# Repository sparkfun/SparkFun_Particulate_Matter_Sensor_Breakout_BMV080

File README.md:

SparkFun Air Quality PM1/PM2.5/PM10 Sensor - BMV080 (Qwiic)
========================================

[*SparkFun Air Quality PM1/PM2.5/PM10 Sensor - BMV080 (Qwiic) (SEN-26554)*](https://www.sparkfun.com/sparkfun-air-quality-pm1-pm2-5-pm10-sensor-bmv080-qwiic.html)

The SparkFun Qwiic Particulate Matter Sensor - BMV080 is an ultra-small, fan-less air quality sensor for sensing PM2.5 particulate matter! Within the enclosure is a breakout board that breaks out Bosch's BMV080, the world's smallest PM1 and PM2.5 air quality sensor. The sensing element measures merely 4.2mm x 3.5mm x 3.1mm (W x L x H), which is more than 450 times smaller than any comparable device on the market. The innovative design is based on ultra-compact lasers with integrated photodiodes. The sensor applies sophisticated algorithms to measure PM1 and PM2.5 concentrations directly in free space, without requiring an intrusive fan.

Repository Contents
-------------------

* **.github/workflows** - YAML files used for GitHub Actions and GitHub Pages/mkdocs
* **/Enclosure** - Enclosure files
* **/Hardware** - KiCad design files (.kicad_pcb, .kicad_sch, .kicad_pro)
  * **/Production** - Production panel files (.kicad_pcb)
* **/docs** - Online documentation files
  * **/assets** - Folder containing all the file assets used for product documentation
    * **/board_files** - Copy of design files used for product documentation
    * **/component_documentation** - Datasheets and manuals for hardware components
    * **/img** - Images for product documentation
  * **/github** - Files stating how to contribute and filing issues used for product documentation
  * **/javascript** - Folder containing custom javascript used for product documentation
  * **/stylesheet** - Folder containing CSS files used for product documentation
* **/overrides** - Customization files used for product documentation
  * **/.icons** - Icons used for GitHub used for product documentation
  * **./partials** - Used for product documentation

Documentation
--------------
* **[Library](https://github.com/sparkfun/SparkFun_BMV080_Arduino_Library/)** - Arduino library for the SparkFun Air Quality PM1/PM2.5/PM10 Sensor - BMV080 (Qwiic).
* **[Hookup Guide](https://docs.sparkfun.com/SparkFun_Particulate_Matter_Sensor_Breakout_BMV080)** - Basic hookup guide for the SparkFun Air Quality PM1/PM2.5/PM10 Sensor - BMV080 (Qwiic).

Product Versions
----------------
* [SEN-26554](https://www.sparkfun.com/products/ - SparkFun Air Quality PM1/PM2.5/PM10 Sensor - BMV080 (Qwiic) 

License Information
-------------------

This product is _**open source**_!

Please review the LICENSE.md file for license information.

If you have any questions or concerns on licensing, please contact technical support on our [SparkFun forums](https://community.sparkfun.com/c/community/general-chit-chat/37).

Distributed as-is; no warranty is given.

- Your friends at SparkFun.

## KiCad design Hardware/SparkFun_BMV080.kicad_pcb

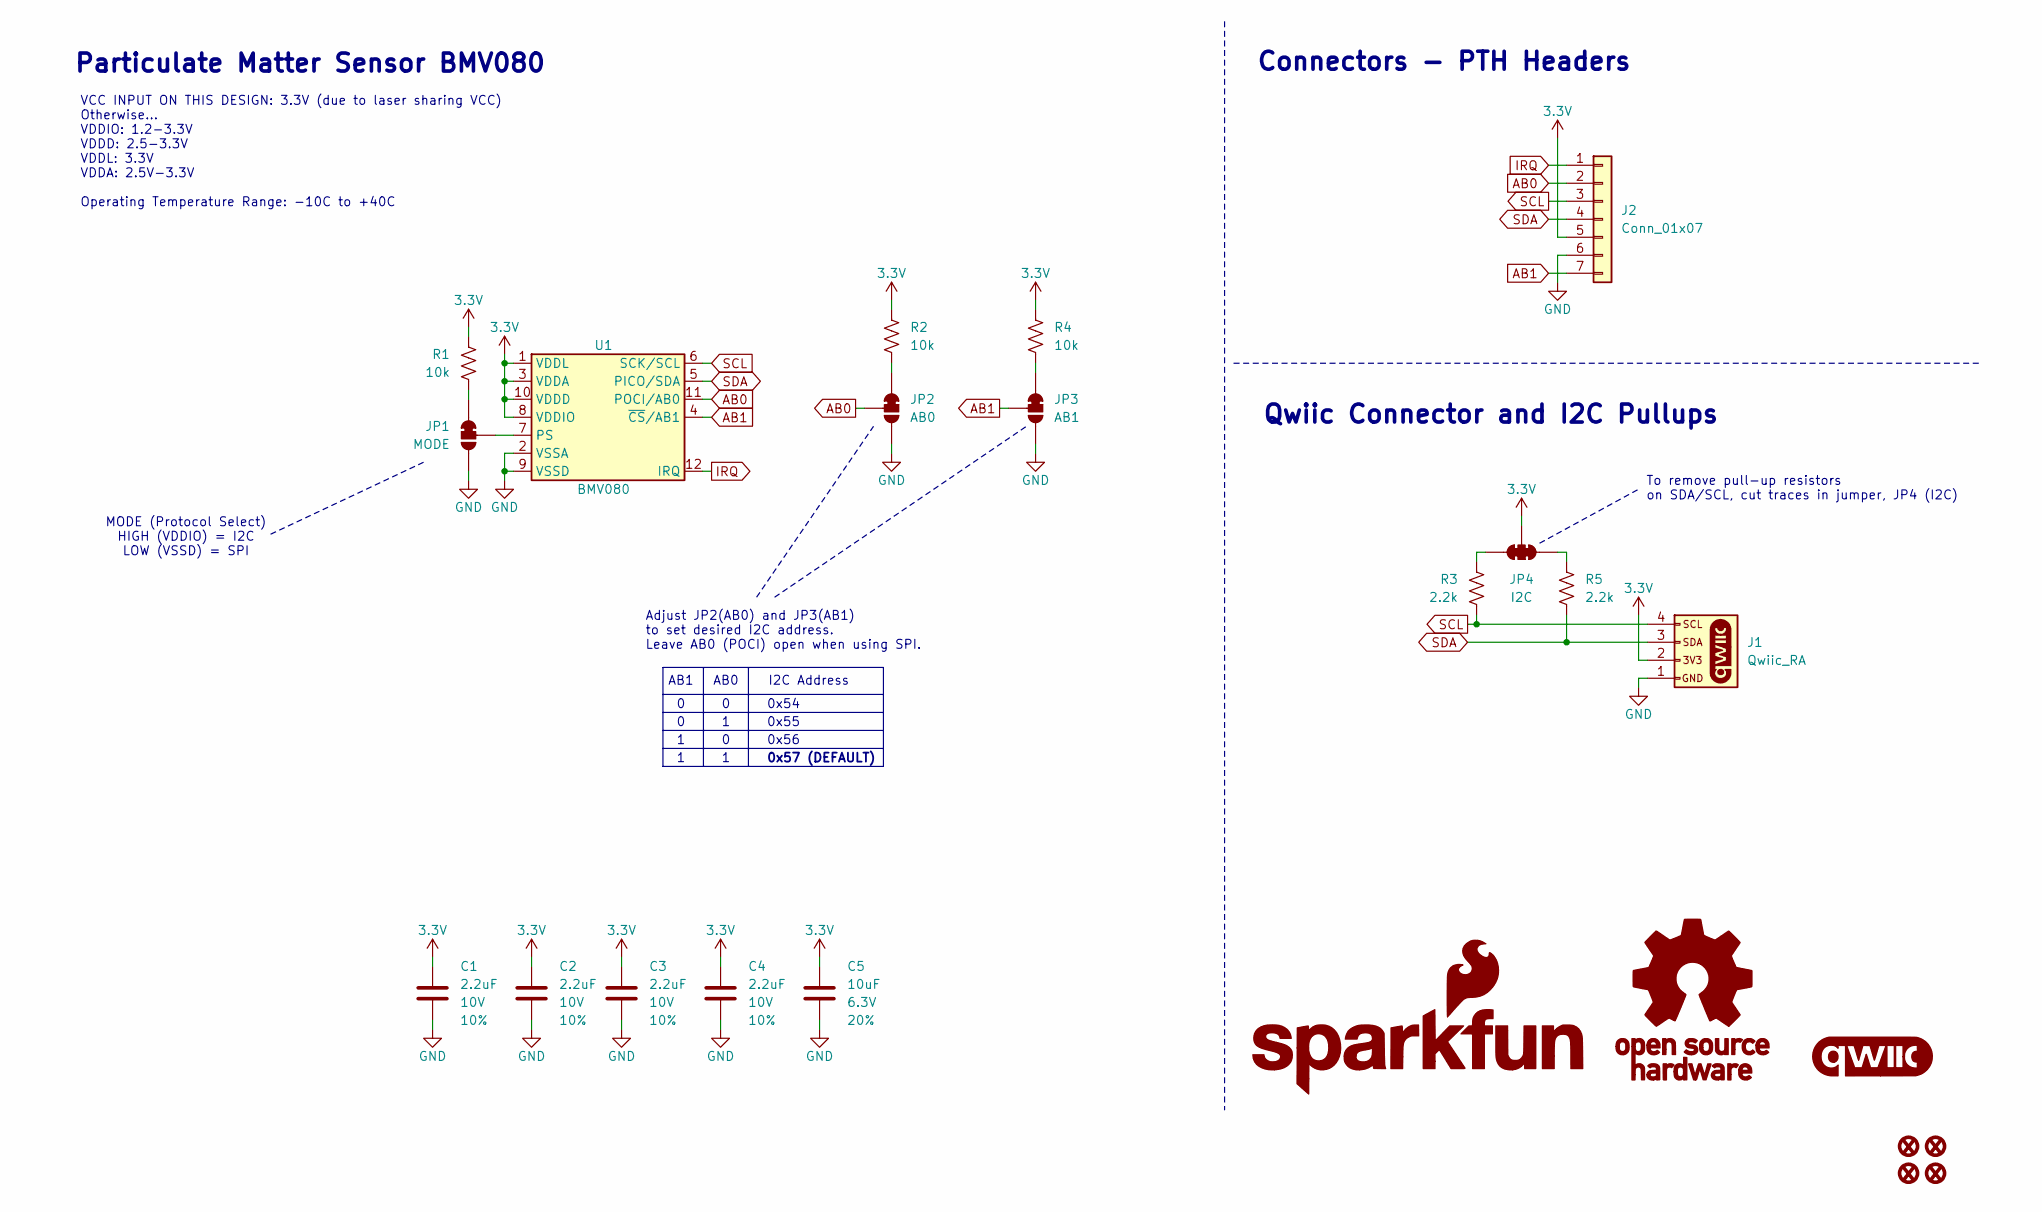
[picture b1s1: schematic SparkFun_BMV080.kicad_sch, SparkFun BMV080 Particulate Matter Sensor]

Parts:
C1, C2, C3, C4: 2.2uF; C_0402_1005Metric; Voltage 10V; Tolerance 10%
C5: 10uF; C_0603_1608Metric; Voltage 6.3V; Tolerance 20%
FID1, FID2, FID3, FID4: Fiducial_0.5mm; Fiducial_0.5mm_Mask1mm
G1: OSHW_Logo; Creative_Commons_License
G2: SparkFun_Logo
G3: qwiic_Logo
J1: Qwiic_RA; JST_SMD_1.0mm-4_RA
J2: Conn_01x07; 1x07
JP1: MODE; Jumper_3_NC-1_Trace_NoSilk
JP2: AB0; Jumper_3_NC-1_Trace_NoSilk
JP3: AB1; Jumper_3_NC-1_Trace_NoSilk
JP4: I2C; Jumper_3_NC-2_Trace_NoSilk
R1, R2, R4: 10k; R_0402_1005Metric
R3, R5: 2.2k; R_0402_1005Metric
U1: BMV080; FPC_0.3mm-13

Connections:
3.3V: C1.1, C2.1, C3.1, C4.1, C5.1, J1.2, J2.5, JP4.2 (C), R1.1, R2.1, R4.1, U1.1 (VDDL), U1.3 (VDDA), U1.8 (VDDIO), U1.10 (VDDD)
AB0: J2.2, JP2.2 (C), U1.11 (POCI/AB0)
AB1: J2.7, JP3.2 (C), U1.4 (~CS/AB1)
GND: C1.2, C2.2, C3.2, C4.2, C5.2, J1.1, J2.6, JP1.3 (B), JP2.3 (B), JP3.3 (B), U1.2 (VSSA), U1.9 (VSSD)
IRQ: J2.1, U1.12 (IRQ)
unnamed: JP1.1 (A), R1.2
unnamed: JP1.2 (C), U1.7 (PS)
unnamed: JP2.1 (A), R2.2
unnamed: JP3.1 (A), R4.2
unnamed: JP4.1 (A), R5.2
unnamed: JP4.3 (B), R3.2
SCL: J1.4, J2.3, R3.1, U1.6 (SCK/SCL)
SDA: J1.3, J2.4, R5.1, U1.5 (PICO/SDA)

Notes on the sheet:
0x54
MODE (Protocol Select) HIGH (VDDIO) = I2C LOW (VSSD) = SPI
AB1
Connectors - PTH Headers
0x57 (DEFAULT)
VCC INPUT ON THIS DESIGN: 3.3V (due to laser sharing VCC) Otherwise... VDDIO: 1.2-3.3V VDDD: 2.5-3.3V VDDL: 3.3V VDDA: 2.5V-3.3V Operating Temperature Range: -10C to +40C
Particulate Matter Sensor BMV080
AB0
0x56
I2C Address
Adjust JP2(AB0) and JP3(AB1) to set desired I2C address. Leave AB0 (POCI) open when using SPI.
0x55
To remove pull-up resistors on SDA/SCL, cut traces in jumper, JP4 (I2C)
Qwiic Connector and I2C Pullups

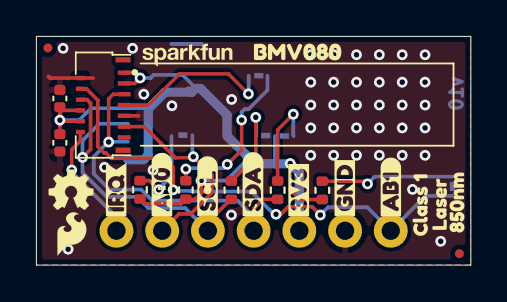
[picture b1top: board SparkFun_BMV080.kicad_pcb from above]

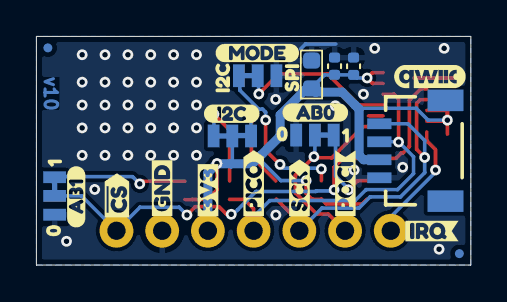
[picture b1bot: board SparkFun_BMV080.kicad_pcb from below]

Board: 2 copper layers, 24.1 x 12.7 mm, 51 parts (27 on the bottom side), 13 nets.

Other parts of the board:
Ref**: Val**; OSHW_Logo_2.5mm
kibuzzard-66BFB450: G***; kibuzzard-66BFB450
kibuzzard-66BFBF9D, kibuzzard-66BFBF9D#2: G***; kibuzzard-66BFBF9D
kibuzzard-66BFBF23: G***; kibuzzard-66BFBF23
kibuzzard-66BFBF70, kibuzzard-66BFBF70#2: G***; kibuzzard-66BFBF70
kibuzzard-66BFC0D2: G***; kibuzzard-66BFC0D2
kibuzzard-66BFC2FE: G***; kibuzzard-66BFC2FE
kibuzzard-66BFC09F: G***; kibuzzard-66BFC09F
kibuzzard-66BFC045: G***; kibuzzard-66BFC045
kibuzzard-66BFC108: G***; kibuzzard-66BFC108
kibuzzard-66BFC288: G***; kibuzzard-66BFC288
kibuzzard-66C3B2A1: G***; kibuzzard-66C3B2A1
kibuzzard-66C3B2DA: G***; kibuzzard-66C3B2DA
kibuzzard-66C3B2FA, kibuzzard-66C3B2FA#2: G***; kibuzzard-66C3B2FA
kibuzzard-66C3B3B1: G***; kibuzzard-66C3B3B1
kibuzzard-66C3B3D3: G***; kibuzzard-66C3B3D3
kibuzzard-66C3B30A, kibuzzard-66C3B30A#2: G***; kibuzzard-66C3B30A
kibuzzard-66C3B31E: G***; kibuzzard-66C3B31E
kibuzzard-66C3B369: G***; kibuzzard-66C3B369
kibuzzard-66C4B81D: G***; kibuzzard-66C4B81D
kibuzzard-66C7A36E: G***; kibuzzard-66C7A36E
kibuzzard-66C77290: G***; kibuzzard-66C77290
kibuzzard-67250BE2: G***; kibuzzard-67250BE2
kibuzzard-67250CD2: G***; kibuzzard-67250CD2
kibuzzard-67250CEE: G***; kibuzzard-67250CEE

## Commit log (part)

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2024-08-16 Layout work
2024-08-19 moved hw files into Hardware folder
2024-08-19 updated gitignore
2024-08-19 moved step file
2024-08-19 schematic cleanup and reroute
    -added section divider lines and section titles
    -jumper reference and naming corrected, rotated text in sch to all horizontal
    -added company and defined by:
    -rearranged part name and value texts for calrity
    -moved logos in sch to proper location
    -moved to vertical qwiic connector
2024-08-20 changed bypass caps to larger value of 2.2uF
    -bypass caps bumped up from 1.0uF to 2.2uF as per recommended in datasheet
2024-08-20 jumpers to no silk outline and prod_id on ic
2024-08-20 measures and more
    -add measures
    -add copper finish
    -add ordering instructions
    -DRC fixes
2024-08-20 grid and molex connector FP correction
    -set grid origin point to top left of PCB edge
    -corrected molex connecto FP - width of mounting pads X position was 2.52 and now is 2.51
2024-08-20 nudged via next to mounting pad for DRC correction
2024-08-20 molex connector outline in FP
2024-08-20 molex fp work
    -removed extra **VAL text object
    -moved INSERT THIS END to user.1
    -added connector ds link in the FP
2024-08-20 molext connector ds link in fp
2024-08-20 corrected position of NC pin 13 in symbol
2024-08-20 CSB is active low in symbol
2024-08-20 drc exlusions
2024-08-21 pre-review last second updates
    -added VCC input requirements and ranges into sch
    -added temp range to sch
    -added pin 1 indicator silk to molex connector
    -added extra GRND trace connection on pad 2 of molex connector
2024-08-21 sensor position outline correction and more
    -added F.Fab and F.Silk outline for sensor - to help with correctly showing position on PCB
    -changed PROD_ID to connector for the sensor
    -made v01 in copper "knockout" style
    -adjusted F.Mask to match the area of the sensor we are supposed to use thermal tape on
    -adjusted B.Mask to match our small heat sink.
2024-08-21 added SFE and OSHW logos
2024-08-21 dimensions update and resistor line up
2024-08-21 moved AB1/CS header onto 0.5 grid for perf board/breadboard
2024-08-21 DRC exclusions
2024-08-22 checklist run eng
    -sch tightening
    -sch jumpers text notes
    -set solder mask expansion to 0.05mm
    -added active low line on top of CS label silk
    -SCL silk label set to input end flag type
2024-08-22 Initial Push GitHub Pages
2024-08-22 acid trap fix on gnd connection coming off Molex
2024-08-22 -tiny tweaks before ordering v01
    -updated measures on AB1 header
    -updated F.FAB drawing of plastic on molex to better estimate reflow position
    -moved NC into symbol box to avoid accidentally netting to it
    -CSB is now CS with a line
    -SCK clock silk label is round
2024-08-22 proto panel 2x2 of v01
2024-08-23 panel v01b - meet size requirement for vscores
    -expanded outer tabs to meet 70mmx70mm requirement for vscores
2024-10-21 housing design - slot style v26
2024-10-22 v27 slight enlarging of slots
2024-11-01 v02 pcb protos v29a enclosure
    -RA qwiic connector
    -removed standoffs
    -single pth header row now includes CS
    -moved pth header upwards to clear enclosure slot
    -decreased width from 1 inch to 0.95 inch
2024-11-01 PCB dimensions updated/added
2024-11-01 update libraries and 3d models
2024-11-04 mounting flanges
2024-11-06 flange tweaking
2024-11-14 bumping version to v10
2024-11-14 removing FreeCAD backup files
2024-11-14 pre-review changes
    -adjusted 3.3V pads route away on FPC to avoid oddities and promote even reflow.
    -added gnd via near AB1 header to avoid GND pour antenna.
    -pulled trace away from I2C jumper to avoid slicing.
    -nudged via to avoid acid trap near AB0 jumper.
    -nudges via near SDA pad on FPC to avoid acid trap
2024-11-14 FPC 3d model position correction
2024-11-14 Added sensor 3d model
2024-11-15 Update 3D model
2024-11-25 Changed C5 from DNP to populated
2024-11-25 ordering instructions updated to RED
2024-11-25 production pcb panel v10
2024-11-26 V32 housing - unify parts and exported STL files
    -V32 housing design verified on inhouse resin printer
    -unified (aka Fusion in freeCAD) bodies to a single body for mesh export as STL
    -utilized higher precision settings for TSL export (surface dev: 10um, angular dev: 10deg)
    -created ZIP file of both STL files (inner and outer shell) for quotes
2024-11-26 demo mounting board design WIP
2024-12-11 housing - re-created stl files for proto order 1 from JLC
    -these files were used on the 1st proto order from jlc3dp
    -they are a single shell and have higher output resolution
    -renamed to smaller length name (JLC didn't like long name on the upload)
2024-12-11 demo mounting board DXF v02
    -switched BMV080 and alphanewmeric display, so BMV080 is on the left. This will work better with any text I raster into the plexiglass plate.
2024-12-12 demo board mesh outputs as STL
2024-12-19 demo mounting board update for oled 1.3 inch
2024-12-19 o-ring slot mount cover created
    -designed around the actual 1:1 dimensions of the o-ring.
    -note to self, still has conflict with PCB end stop on outer shell
2024-12-20 o-ring cover slot box, and pcb slot tightening
    -Changed to o-ring style "cover slot box"
    -Width of PCB slot was 14.2, now is 13.8.
    -Height of PCB flex mounds was 0.25mm, now is 0.45mm
2024-12-20 tightening of outer shell cavity
    -reduced x and y each by 0.2mm (was 17.8x28.14, now is 17.6x27.94)
2024-12-20 thre varieties of oring placement dot versions
    1 dot = oring tangent to glass
    2 dot = oring lowered 0.1mm
    3 dot = oring lowered 0.2mm
2024-12-20 increased QWIIC connector wall opening width
    -qwiic wall opening now 7.3mm (both inner and outer shells
2024-12-20 Outershell version "0D"
2024-12-21 Outer shell snap fit pin hole mod
    SFE_BMV080_OS_1D = snapfit pin updated to accept wider "rail" snap fit type.
2024-12-21 IS_4D - tightest snap fit pin rail style
2024-12-21 IS_5D Medium tightness snap fit pin rail style
2024-12-21 IS_5D least tightness snap fit rail style
2025-01-07 flex mounds increased to a true 0.45mm height
    -previously, they were actually 0.38mm (the bezie position dot above the line was 0.45mm)
2025-01-09 mods to allow vertical placement
    -adjusted design to allow for glass and o-ring to mount to inner shell vertically (previous designs had these enter the cavities by sliding sideways into the slots.
    -adjusted outer shell opening to mate with top side of o-ring and clear "o-ring_glass_mount_bottom" box
    -adjusted snapfit pin and holes for smoother compression. Now has an "entrance ramp" (cut from the walls of the outer shell) to begin the compression of the inner shell walls as it moves upward into 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
2025-01-09 IS_VM_1D
    IS_VM_1D:
    snap-fit pin Z_pos = snap-fit hole Z_pos
    snap-fit pin H = 0.5mm
    pcb-flex-mound H = 0.45mm
2025-01-09 IS_VM_2D
    IS_VM_2D:
    snap-fit pin Z_pos = snap-fit hole Z_pos
    snap-fit pin H = 0.6mm
    pcb-flex-mound H = 0.55mm
2025-01-09 IS_VM_3D
    IS_VM_3D:
    snap-fit pin Z_pos = snap-fit hole Z_pos
    snap-fit pin H = 0.7mm
    pcb-flex-mound H = 0.65mm
2025-01-09 OS_VM_1D
    OS_VM_1D:
    snap-fit HOLE Z_pos = snap-fit PIN Z_pos
2025-01-09 OS_VM_2D
    OS_VM_2D:
    snap-fit HOLE Z_pos = (snap-fit PIN Z_pos + 1mm)
2025-01-09 added qwiic connector cutout to OS_VM_2D
2025-01-10 mod sensor opening cut to avoid thin area
2025-01-16 added openings to pry open outer shell more easily
    -version dots updated to 4 dots
    -added openings to pin cavities to slide in flat head precision screw driver more easily to open this up if needed.
2025-01-17 fine tunes flathead cavity
    -opened up the cavity a bit more for the flathead screwdriver to fit in.
    -updated mesh STL for 4D version
2025-01-20 OS_VM_5D - flame/bmv080 text on outer shell
2025-01-27 scooted sensor opening over 0.5mm for better alignment with reality
    -adjusted sensor_opening_cut_OS, so that the opening is 0.5mm closer to the edge, to better align with the actual position of the sensor in reality.
2025-01-27 OS_VM_5D Mesh export
2025-01-30 Add Some Assets
2025-01-30 separating out OS to its own file
    -bringing OS to its own file, for easier merging later
    -created "assembly" file that will contain (via A2plus) both the IS, OS and other parts to show fit between models
2025-01-30 bringing in IS_VM_6D
    -Note, the inner shell is now its own file
    -also updates sub-models as necessary for IS_VM_6D design to be current
    -added HMV080_Enclosure_Inner_Shell.FCStd to assembly file via A2plus
2025-01-30 cleanup of old files
2025-01-31 PTH Header fillet slot opening
    -added a slot to the inner shell, to allow clearance for when using PTH male header pins.
    -Also added a "thickener" bit of material above the slot, so that the wall will fab better.
    -Also cut out a cavity of the outer shell to allow space for the new thickener rectangle.
2025-01-31 Final edits - ready to order production parts
    -updated flame size/location
    -changed to version "v10" text cutout of each part
    -exported mesh (STL)
    -changed color of appearance on mounting flanges - just for some rendering screen shots.
2025-01-31 ordering instructions and ZIP
2025-02-04 Corrected thin wall on IS (under glass mount)
    -Corrected a thin wall near the sensor opening.
    -This was caused when I scooted the sensor opening over 0.5mm, but failed to also scoot over the "slot-cut" material below.
    -bumped the version text cutter to v11 (inside shell design only)
    -exported mesh
    -zipped with ordering instructions.
2025-02-04 updates sub-designs to IS6_OS5
    -Updating a few files of sub-designs, for a cleaner/easier merge of branch IS6_OS5 into main
2025-02-05 Update product name
2025-02-05 Add Arduino Examples and Break Up Sections
2025-02-05 Add Instructions Removing Enclosure & Reassembling
2025-02-05 Add Additional Hookup Accessories
2025-02-06 Add quickstart guide
2025-02-10 ISv12, OSv11, wall thickening
    -The left/right walls of the o-ring mount were 0.66mm thick (which is below JLCs threshold [0.8mm]). They are now 1.05mm.
    -opened up OS cavity above the o-ring mount box to work with the modified IS.
    -also adjusted the version text cutouts to be less deep - to avoid wall thickness warnings.
2025-03-20 Enclosure files organized by file type (STEP/FreeCAD/STL)
2025-03-21 library work
    -moved bmv080 sensor symbol and footprint to sparkfun libraries with pending PR.
    -updated symbol and footprints in kicad design files
    -note, the sensor itself and the FPC connector are now separate things. The BMV080 has an "outline" footprint that is placed at the same origin point as the sensor (and includes the 3d model of the s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
2025-03-25 Docs pre-review update
    Adding photo assets & screenshots. Edits to most docs files and initial review changes.
2025-03-25 Build error fix
    Replacing GH pages build file & minor edits to Readme & other pages.
2025-03-25 Deployed 3e505ad with MkDocs version: 1.6.1
2025-03-26 Update README.md
    Fixing image size
2025-03-26 Deployed 2e2d411 with MkDocs version: 1.6.1
2025-03-26 Update README.md
    Fixing image link to product page.
2025-03-26 Deployed ac6a376 with MkDocs version: 1.6.1
2025-03-27 Update quickstart.md
    Fixing quick start assembly image size & adding links for OLED & Alphanumeric examples.
2025-03-27 Deployed 670a57d with MkDocs version: 1.6.1
2025-03-28 Update STEP file
    -step file now includes the 3d model of the sensor
    -also updated some library work around the FPC and sensor step files
2025-03-28 Deployed 9835d55 with MkDocs version: 1.6.1
2025-03-28 updating GLP 3dmodel file
2025-03-28 Deployed 606344b with MkDocs version: 1.6.1
2025-04-02 Arduino library updates
    Updating Quick start & Arduino Set Up pages with updated instructions on adding SDK to Arduino library.
2025-04-02 Deployed bf2b243 with MkDocs version: 1.6.1
2026-06-03 Deployed 0e24af8 with MkDocs version: 1.6.1
2026-06-09 Docs formatting update
    Updating docs to remove center tags.

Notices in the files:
parts and their libraries:
Released under the Creative Commons Attribution Share-Alike 4.0 License
https://creativecommons.org/licenses/by-sa/4.0
